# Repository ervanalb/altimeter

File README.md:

# altimeter
Audible altimeter for skydiving

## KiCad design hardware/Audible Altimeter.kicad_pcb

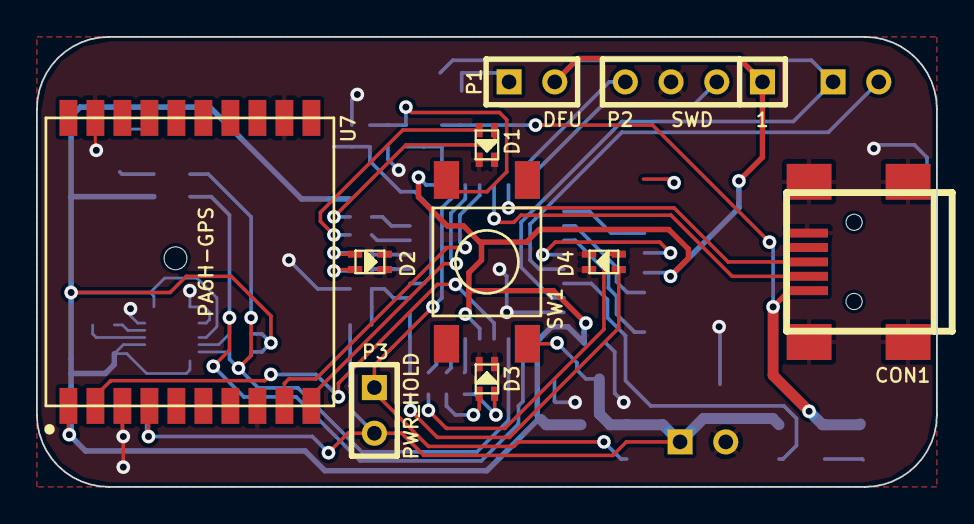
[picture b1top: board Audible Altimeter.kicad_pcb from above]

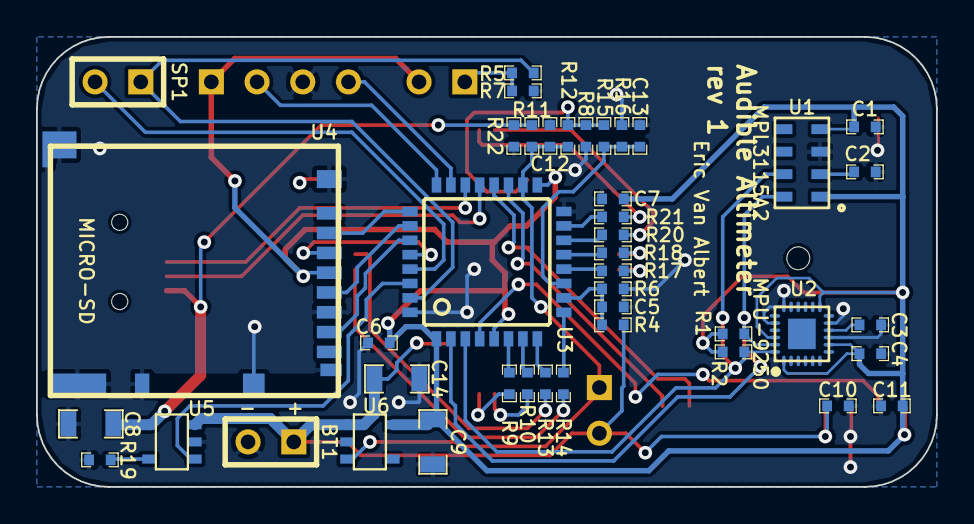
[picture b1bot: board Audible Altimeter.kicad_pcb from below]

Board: 2 copper layers, 50.0 x 25.0 mm, 53 parts (43 on the bottom side), 44 nets.

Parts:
BT1: BATTERY; SIL-2
C1, C2, C3, C4, C5, C6, C7, C10, C11, C12, C13: 100n; SA0402
C8, C14: 1u; SA0805
C9: 2u2; SA0805
CON1: USB-MINI-B; USB_MINI_B
D1, D2, D3, D4: DUAL_LED; SA0605_DUAL_LED
P1: BOOT; SIL-2
P2: SWD; SIL-4
P3: PWR_HOLD; SIL-2
R1, R2, R15: 4K7; SA0402
R4: 1M; SA0402
R5, R7, R16: 10K; SA0402
R6: 2.2M; SA0402
R8, R22: 2K2; SA0402
R9, R10, R13, R14, R17, R18, R20, R21: 68R; SA0402
R11, R12: 100K; SA0402
R19: 2K; SA0402
SP1: PIEZO; SIL-2
SW1: BUTTON; TACT-SW-SMD
U1: MPL3115A2; LGA_8
U2: MPU-9250; 24-QFN_3x3
U3: STM32F042-32; LQFP32
U4: MICRO-SD; DM3BT
U5: MCP73831; SOT23-5
U6: MCP1824; SOT23-5
U7: PA6H-GPS

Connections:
+5V: C8.1, CON1.1, R11.1, R22.2, U5.4
+BATT: BT1.1, C10.1, C14.1, P3.2, R4.1, SW1.2, U5.3, U6.1, U7.4
/BATT_MEAS: C5.1, R4.2, R6.2, U3.10
/BUTTON: C13.1, R15.2, R16.2, U3.11
/CHARGING: U3.30, U5.1
/GPS_RX: U3.19, U7.10
/GPS_TX: U3.20, U7.9
/LED1: R9.1, U3.6
/LED2: R10.1, U3.7
/LED3: R13.1, U3.8
/LED4: R14.1, U3.9
/LED5: R17.1, U3.12
/LED6: R18.1, U3.13
/LED7: R20.1, U3.14
/LED8: R21.1, U3.15
/PWR_ON: C12.1, P3.1, R11.2, R12.2, U3.18, U6.3
/RESET: U3.4, U7.2
/SCL: R1.2, U1.8, U2.23, U3.2
/SDA: R2.2, U1.7, U2.24, U3.3
/SPI_CS: U3.25, U4.2
/SPI_MISO: U3.27, U4.7
/SPI_MOSI: U3.28, U4.3
/SPI_SCK: U3.26, U4.5
/SWCLK: P2.2, U3.24
/SWDAT: P2.4, U3.23
/USB_DM: CON1.2, U3.21
/USB_DP: CON1.3, U3.22
GND: BT1.2, C1.2, C2.2, C3.2, C4.2, C5.2, C6.2, C7.2, C8.2, C9.2, C10.2, C11.2, C12.2, C13.2, C14.2, CON1.5, CON1.6, CON1.7, CON1.8, CON1.9, D1.2, D1.4, D2.2, D2.4, D3.2, D3.4, D4.2, D4.4, P2.3, R6.1, R7.2, R8.2, R16.1, R19.2, R22.1, U1.3, U2.9, U2.11, U2.18, U2.20, U3.16, U3.32, U4.6, U4.9, U4.10, U4.11, U4.12, U4.13, U4.14, U5.2, U6.2, U7.3, U7.8, U7.12, U7.19
unnamed: C3.1, U2.10
unnamed: D2.3, R18.2
unnamed: D2.1, R17.2
unnamed: D1.1, R20.2
unnamed: D1.3, R21.2
unnamed: D3.1, R9.2
unnamed: D3.3, R10.2
unnamed: D4.1, R13.2
unnamed: D4.3, R14.2
unnamed: SP1.2, U3.29
unnamed: R19.1, U5.5
unnamed: C2.1, U1.2
unnamed: R5.2, SP1.1, U3.31
unnamed: P1.1, R5.1, R7.1
unnamed: R8.1, R12.1, R15.1, SW1.3
VDD: C1.1, C4.1, C6.1, C7.1, C9.1, C11.1, P1.2, P2.1, R1.1, R2.1, U1.1, U1.4, U2.1, U2.8, U2.13, U2.22, U3.1, U3.5, U3.17, U4.4, U6.5, U7.1

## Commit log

2015-10-07 add kicad, maybe
2015-10-07 add firmware, maybe
2015-10-07 barometer works (but schematic is wrong, SDA and SCL swapped at micro)
2015-10-09 make slide whistle, begin work on SD card
2015-10-09 sd card works, at least a little bit
